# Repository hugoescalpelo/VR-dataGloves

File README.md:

# VR-dataGloves
All designs and codes for VR Data Gloves

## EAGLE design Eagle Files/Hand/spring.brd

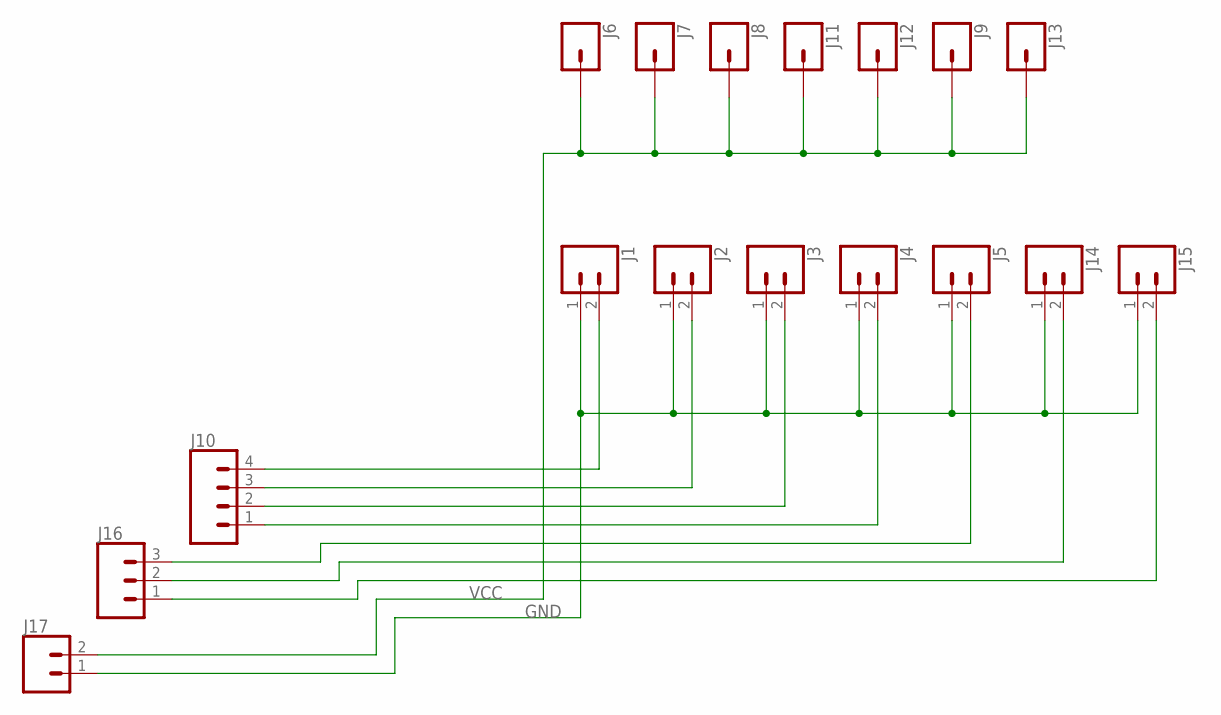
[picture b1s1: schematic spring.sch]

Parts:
J1, J2, J3, J4, J5, J14, J15, J17: CONN_02; 1X02
J6, J7, J8, J9, J11, J12, J13: CONN_01OFFSET; 1X01_OFFSET
J10: CONN_04; 1X04
J16: CONN_03; 1X03

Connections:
GND: J1.1, J2.1, J3.1, J4.1, J5.1, J14.1, J15.1, J17.1
unnamed: J15.2, J16.1
unnamed: J14.2, J16.2
unnamed: J5.2, J16.3
unnamed: J4.2, J10.1
unnamed: J3.2, J10.2
unnamed: J2.2, J10.3
unnamed: J1.2, J10.4
VCC: J6.1, J7.1, J8.1, J9.1, J11.1, J12.1, J13.1, J17.2

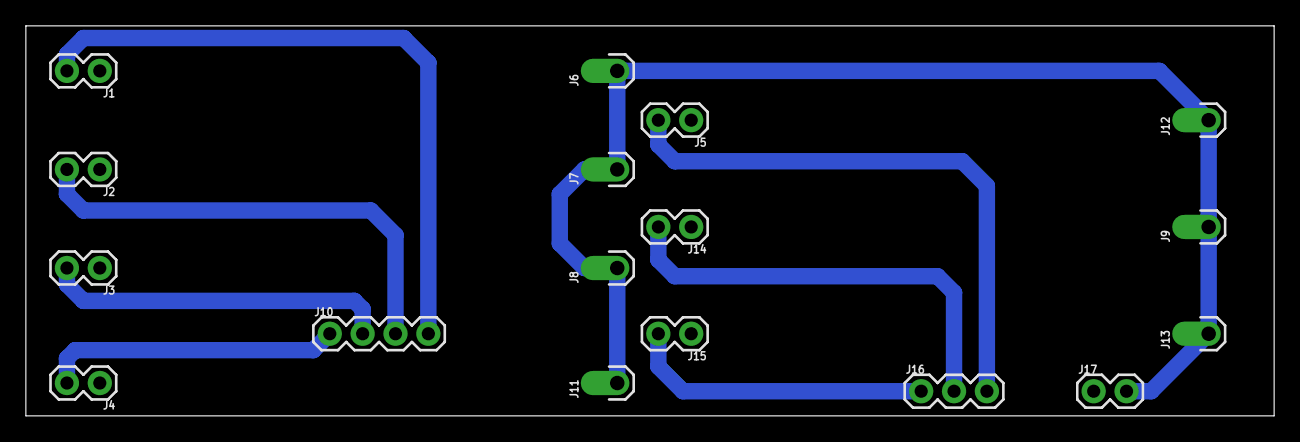
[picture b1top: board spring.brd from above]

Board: 2 copper layers, 96.5 x 30.1 mm, 17 parts (0 on the bottom side), 9 nets.

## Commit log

2019-12-16 First release
    First file release :D
2020-08-19 Create README.md
    First readme commit

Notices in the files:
parts and their libraries:
SparkFun-Connectors: Licensing: Creative Commons ShareAlike 4.0 International - https://creativecommons.org/licenses/by-sa/4.0
